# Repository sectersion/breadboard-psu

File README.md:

# breadboard-psu
simple breadboard psu in a 20x20mm pcb

## features
 - USB-C PD
 - ~2A current limit
 - 4 power output pins
 - tiny!

## AI policy
no ai was used in this project

## devlogs

### devlog 1: this morning
did schematic starting from usb-c receptacle and working down towards power pins
looked at a few datasheets
chose LM whatever 12V-5V ldo for input range

time: 1.5 hours

### devlog 2: this morning 2
finished up pcb, finished up project
did some housekeeping routing and just cleaned up
i still need to make the 3d models, round edges, and create a BOM and stuff

total time: 1 hour-

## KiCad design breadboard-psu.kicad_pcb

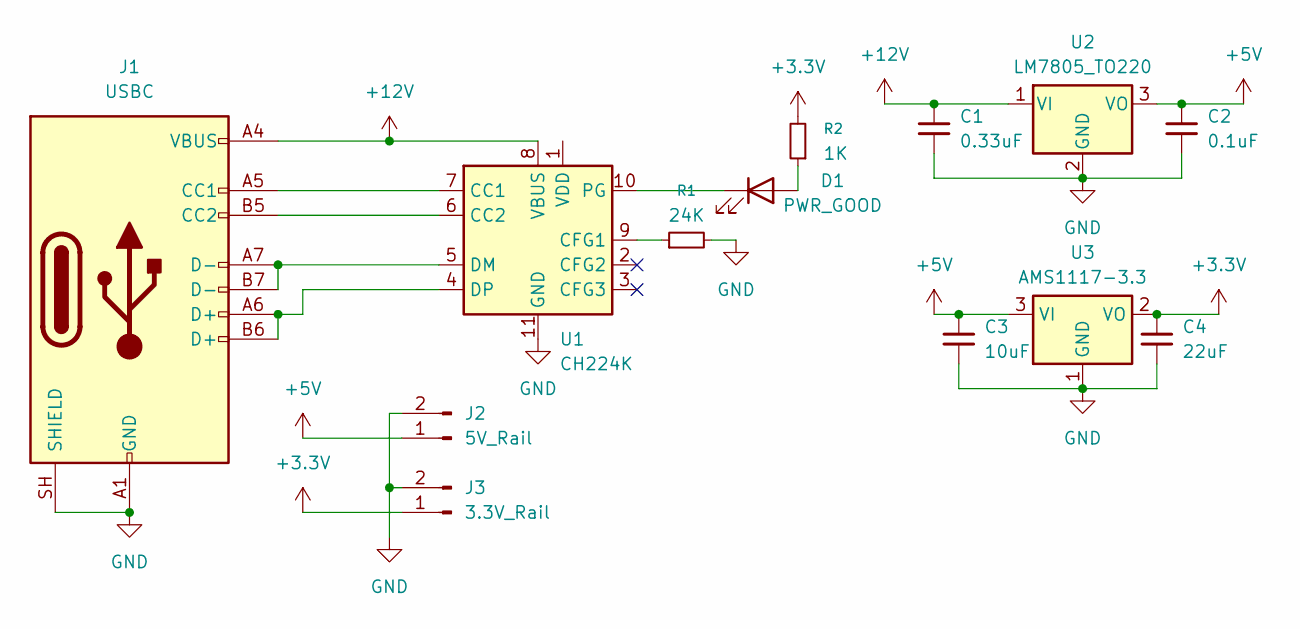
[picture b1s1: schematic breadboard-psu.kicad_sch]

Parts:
C1: 0.33uF; C_0603_1608Metric
C2: 0.1uF; C_0603_1608Metric
C3: 10uF; C_0603_1608Metric
C4: 22uF; C_0603_1608Metric
D1: PWR_GOOD; LED_0603_1608Metric
J1: USBC; USB_C_Receptacle_HRO_TYPE-C-31-M-12
J2: 5V_Rail; PinHeader_1x02_P2.54mm_Vertical
J3: 3.3V_Rail; PinHeader_1x02_P2.54mm_Vertical
R1: 24K; R_0603_1608Metric
R2: 1K; R_0603_1608Metric
U1: CH224K; SSOP-10-1EP_3.9x4.9mm_P1mm_EP2.1x3.3mm
U2: LM7805_TO220; TO-220-3_Vertical
U3: AMS1117-3.3; SOT-223-3_TabPin2

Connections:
+3.3V: C4.1, J3.1, R2.2, U3.2 (VO)
+5V: C2.1, C3.1, J2.1, U2.3 (VO), U3.3 (VI)
+12V: C1.1, J1.A4 (VBUS), J1.A9 (VBUS), J1.B4 (VBUS), J1.B9 (VBUS), U1.8 (VBUS), U2.1 (VI)
GND: C1.2, C2.2, C3.2, C4.2, J1.A1 (GND), J1.A12 (GND), J1.B1 (GND), J1.B12 (GND), J1.SH (SHIELD), J2.2, J3.2, R1.2, U1.11 (GND), U2.2 (GND), U3.1 (GND)
unnamed 4: D1.2 (A), R2.1; also elsewhere on the board
unnamed 5: D1.1 (K), U1.10 (PG); also elsewhere on the board
unnamed: J1.A5 (CC1), U1.7 (CC1)
unnamed: J1.B5 (CC2), U1.6 (CC2)
unnamed: R1.1, U1.9 (CFG1)
unnamed: J1.A7 (D-), J1.B7 (D-), U1.5 (DM)
unnamed: J1.A6 (D+), J1.B6 (D+), U1.4 (DP)

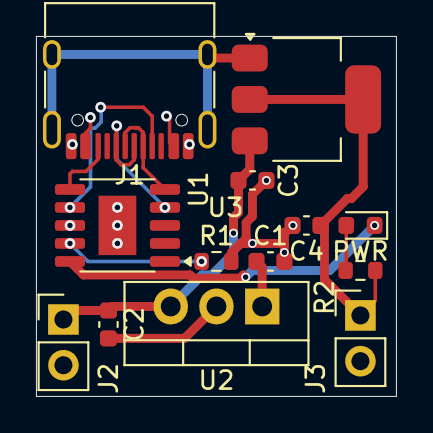
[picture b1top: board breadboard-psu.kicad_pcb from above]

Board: 4 copper layers, 20.0 x 20.0 mm, 13 parts (0 on the bottom side), 11 nets.

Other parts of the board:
PWR: PWR_GOOD; LED_0603_1608Metric

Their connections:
unnamed 4: PWR.2 (A); also elsewhere on the board
unnamed 5: PWR.1 (K); also elsewhere on the board
